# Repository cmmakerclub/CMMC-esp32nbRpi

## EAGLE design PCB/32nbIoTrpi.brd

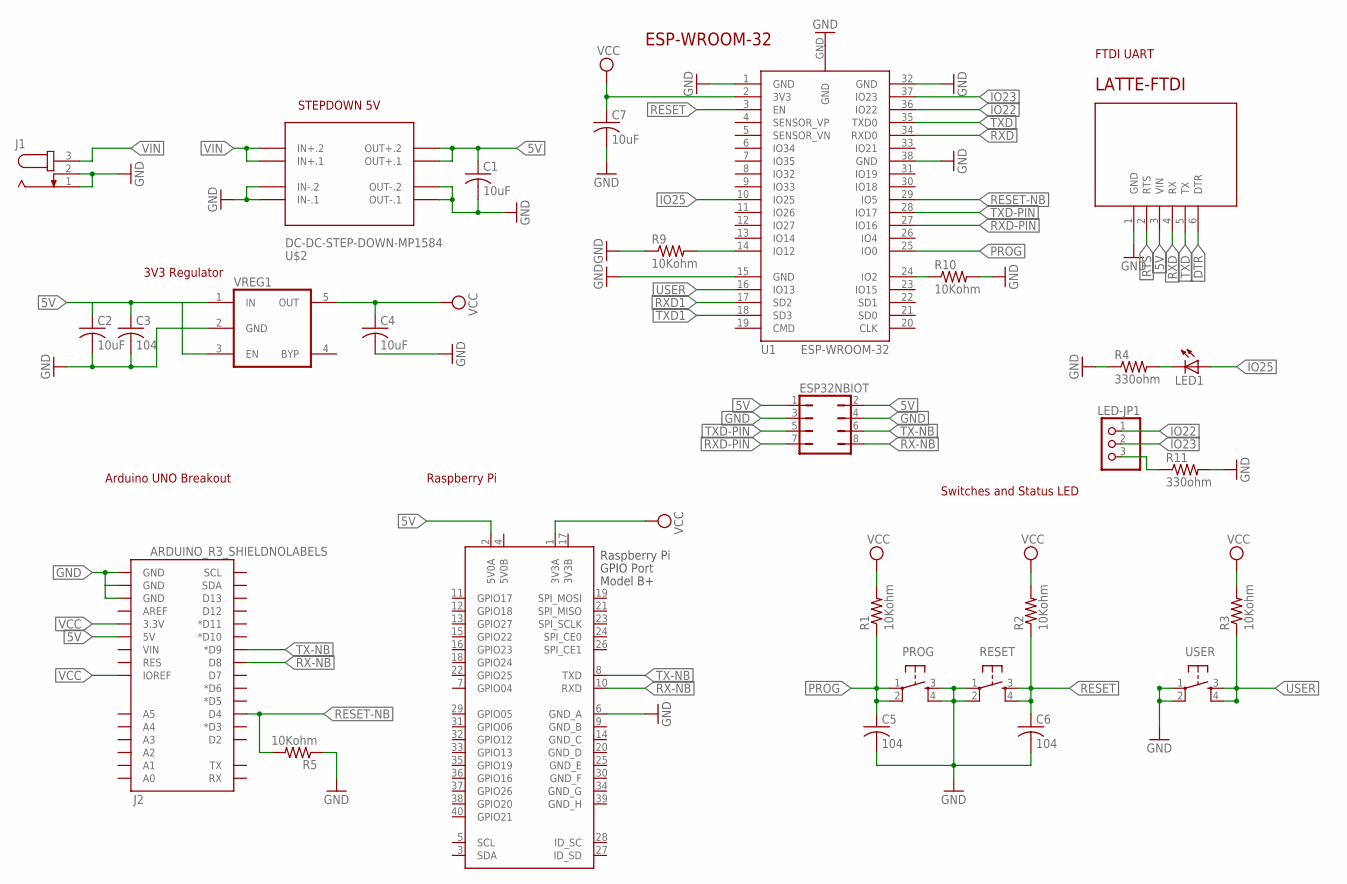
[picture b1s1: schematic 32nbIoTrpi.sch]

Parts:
C1, C2, C4, C7: 10uF; C0805
C3, C5, C6: 104; C0805
ESP32NBIOT: JP4Q
J1: JACK-PLUG1; SPC4078
J2: ARDUINO_R3_SHIELDNOLABELS; UNO_R3_SHIELD_NOLABELS
LATTE-FTDI: FTDI; CMMC-FTDI
LED1: LEDCHIPLED_0805; CHIPLED_0805
LED-JP1: PINHD-1X3/90; 1X03/90
PROG: TAC_SWITCHPTH; TACTILE-PTH
R1, R2, R3, R5, R9, R10: 10Kohm; R0805W
R4, R11: 330ohm; R0805W
RESET: TAC_SWITCHPTH; TACTILE-PTH
U1: ESP-WROOM-32
U$2: DC-DC-STEP-DOWN-MP1584
USER: TAC_SWITCHPTH; TACTILE-PTH
VREG1: VREG_5PINS-SOT-23-5; SOT-23-5
X2: RASPI_BOARD_B+#_E0; RASPI_BOARD_B+_EDGES_0DRILL

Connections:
3V3B: X2.17 (3V3B)
5V: C1.1, C2.1, C3.1, ESP32NBIOT.1, ESP32NBIOT.2, J2.5V, LATTE-FTDI.3 (VIN), U$2.OUT+.1, U$2.OUT+.2, VREG1.1 (IN), VREG1.3 (EN), X2.2 (5V0A)
5V0B: X2.4 (5V0B)
DTR: LATTE-FTDI.6 (DTR)
GND: C1.2, C2.2, C3.2, C4.2, C5.2, C6.2, C7.2, ESP32NBIOT.3, ESP32NBIOT.4, J1.1, J1.2, J2.GND@0 (GND), J2.GND@1 (GND), J2.GND@2 (GND), LATTE-FTDI.1 (GND), PROG.3, PROG.4, R4.1, R5.1, R9.1, R10.2, R11.2, RESET.1, RESET.2, U1.1 (GND), U1.15 (GND), U1.32 (GND), U1.38 (GND), U1.GND, U$2.IN-.1, U$2.IN-.2, U$2.OUT-.1, U$2.OUT-.2, USER.1, USER.2, VREG1.2 (GND), X2.6 (GND_A)
GND_B: X2.9 (GND_B)
GND_C: X2.14 (GND_C)
GND_D: X2.20 (GND_D)
GND_E: X2.25 (GND_E)
GND_F: X2.30 (GND_F)
GND_G: X2.34 (GND_G)
GND_H: X2.39 (GND_H)
IO22: LED-JP1.1, U1.36 (IO22)
IO23: LED-JP1.2, U1.37 (IO23)
IO25: LED1.A, U1.10 (IO25)
unnamed: R10.1, U1.24 (IO2)
unnamed: R9.2, U1.14 (IO12)
unnamed: LED1.C, R4.2
unnamed: LED-JP1.3, R11.1
PROG: C5.1, PROG.1, PROG.2, R1.1, U1.25 (IO0)
RESET: C6.1, R2.1, RESET.3, RESET.4, U1.3 (EN)
RESET-NB: J2.D4, R5.2, U1.29 (IO5)
RTS: LATTE-FTDI.2 (RTS)
RX-NB: ESP32NBIOT.8, J2.D8, X2.10 (RXD)
RXD: LATTE-FTDI.4 (RX), U1.34 (RXD0)
RXD1: U1.17 (SD2)
RXD-PIN: ESP32NBIOT.7, U1.27 (IO16)
TX-NB: ESP32NBIOT.6, J2.D9 (*D9), X2.8 (TXD)
TXD: LATTE-FTDI.5 (TX), U1.35 (TXD0)
TXD1: U1.18 (SD3)
TXD-PIN: ESP32NBIOT.5, U1.28 (IO17)
USER: R3.1, U1.16 (IO13), USER.3, USER.4
VCC: C4.1, C7.1, J2.3.3V, J2.IOREF, R1.2, R2.2, R3.2, U1.2 (3V3), VREG1.5 (OUT), X2.1 (3V3A)
VIN: J1.3, U$2.IN+.1, U$2.IN+.2

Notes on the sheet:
ESP-WROOM-32
STEPDOWN 5V
3V3 Regulator
Arduino UNO Breakout
FTDI UART
Switches and Status LED
Raspberry Pi

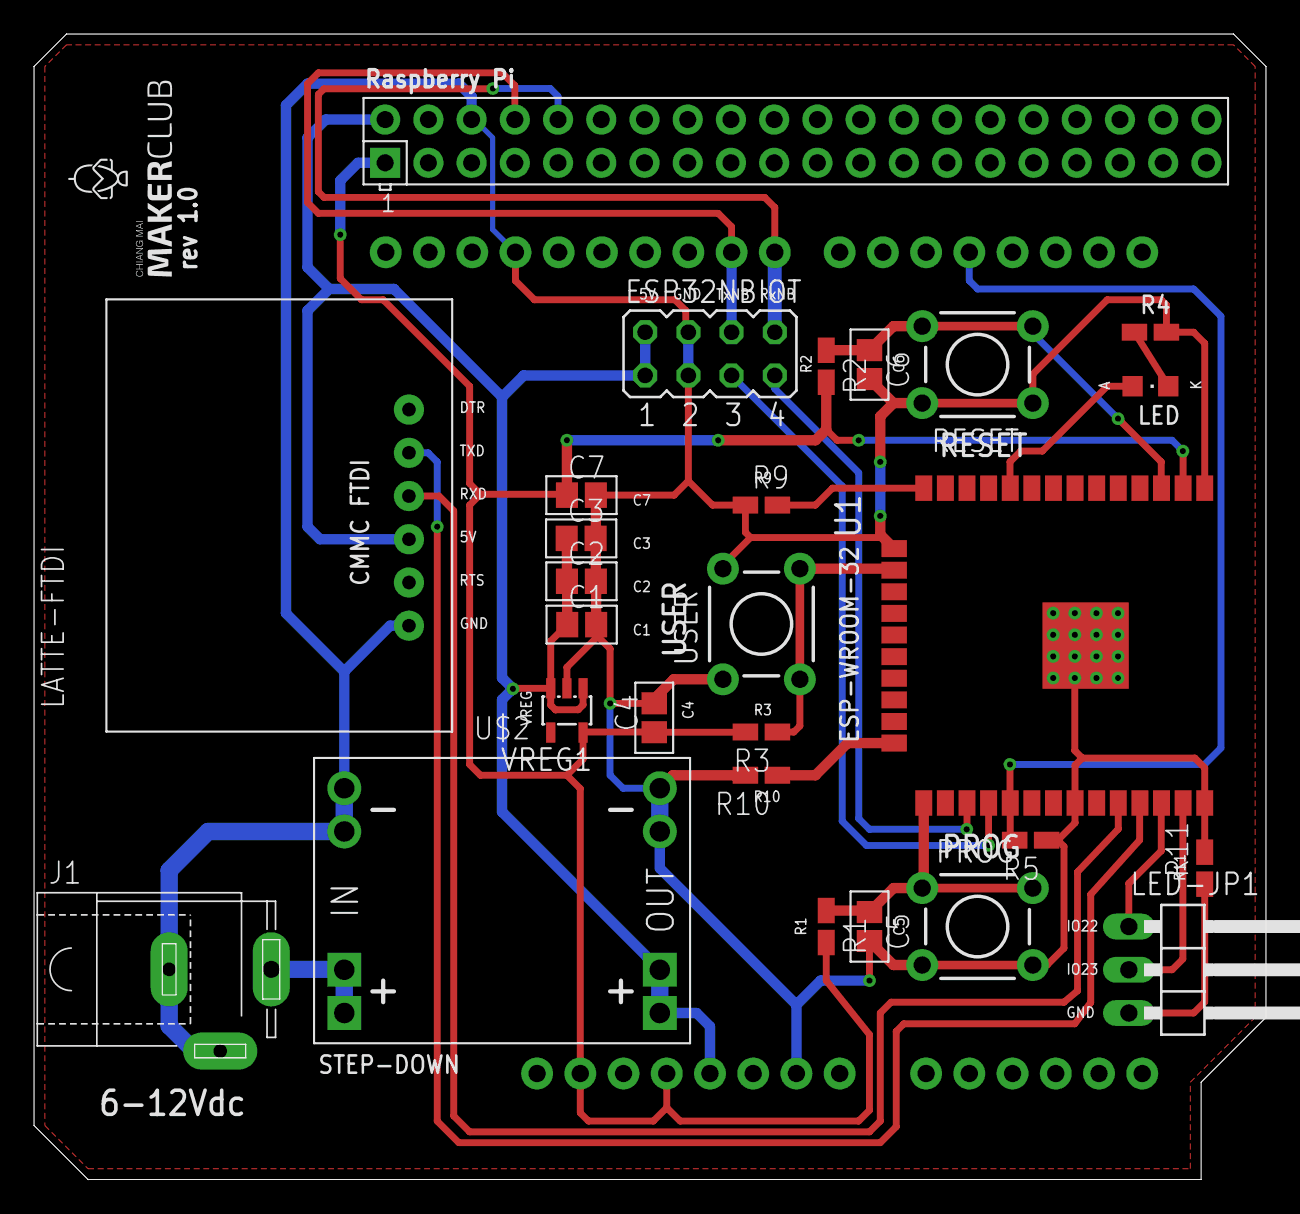
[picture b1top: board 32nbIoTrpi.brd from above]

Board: 2 copper layers, 72.4 x 67.3 mm, 28 parts (0 on the bottom side), 21 nets.

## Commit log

2018-10-17 first commit of free pcb designed

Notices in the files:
parts and their libraries:
SparkFun-Boards: Licensing: Creative Commons ShareAlike 4.0 International - https://creativecommons.org/licenses/by-sa/4.0
diy-modules: Released under the Creative Commons Attribution 4.0 International License: http://creativecommons.org/licenses/by/4.0
